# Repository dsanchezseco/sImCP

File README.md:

# **sImCP**

or *simple ICP* for the friends

sImCP is **custom PCB** powered by an atmega328p to emulate the different aircraft up front controlers (UFC) and input control panels (ICP), mainly a mix of the F-18 and the F-16 panels but with support for others like the AV-8B or the A-10C, for flight simming in DCS an other simulators.

The origin of the project was to have something in the empty space of the MFD in my cockpit, and as such the holes align with the holes and mounting of the Thrustmaster MFDs

The features that define the **sImCP** are:

* Atmega328p
* USB-C
* 21 keys (MX or ALPS mechanical switches)
* 2 encoders with push
* 1 2-Way switch
* 1 4-Way with push and encoder (called dobber)
* [QMK](https://qmk.fm) support
* Thrustmaster Cougar MFD mountable

In fact it is a **fully programmable keyboard** and as such its keys behaviour can be changed by creating a new custom keymap with QMK and flashing it to the board

### It is a keyboard, so use the keyboard column on DCS to do the keybinds

### **Default keymap**

The default keymap has the following keycodes:

```

   ------------ ----------- ------------- ------------- ------------
   |  LCTL+A  | |  LCTL+O  | |  LCTL+U  | |  LCTL+I   | |  LCTL+D  |
   ------------ ------------ ------------ ------------- ------------
   ------------ ------------ ------------ ------------- ------------
   |  RCTL+1  | |  RCTL+2  | |  RCTL+3  | | ENCODER 1 | |  LCTL+H  |
   ------------ ------------ ------------ ------------- ------------
   ------------ ------------ ------------ ------------- ------------
   |  RCTL+4  | |  RCTL+5  | |  RCTL+6  | | ENCODER 2 | |  LCTL+T  | 
   ------------ ------------ ------------ ------------- ------------
   ------------ ------------ ------------ ------------- ------------
   |  RCTL+7  | |  RCTL+8  | |  RCTL+9  | |  2-WAY    | |  LCTL+N  |
   ------------ ------------ ------------ ------------- ------------
   ------------ ------------ ------------ ------------- ------------
   |  RCTL+]  | |  LCTL+0  | |  RCTL+[  | |  DOBBER   | |  LCTL+;  |
   ------------ ------------ ------------ ------------- ------------

#########################################
   ENCODER 1
#########################################
  RCTL+F   LCTL+Q    RCTL+C
   (         |         )
   v         v         v

#########################################
   ENCODER 2
#########################################
  RCTL+Y   LCTL+J    RCTL+G
   (         |         )
   v         v         v

#########################################
   2-WAY
#########################################
  LCTL+K
    ^
    |

    |
    v
  LCTL+X

#########################################
   DOBBER
#########################################
          LCTL+M                     
            ^                        
            |                       RCTL+B   RCTL+W    RCTL+Z 
LCTL+P <-       -> LCTL+R            (         |         )
            |                        v         v         v
            v
          LCTL+W
```

### **Gamepad**

Instead of being recognised as a keyboard the sImCP can be flashed with a custom made firmware to act as a gamepad and output a button instead a keycode on each of the keys. 

**This feature is currently WIP**

### **Flashing** 

To flash a new keymap refeer to the [FIRMWARE README.md](READY%20TO%20USE%20FILES/FIRMWARE/README.md) under the `READY TO USE FILES` folder. The default keymap file is provided as well in the same folder.

### READY TO USE inventory

* PCB_FABRICATION: what's needed to order more to JLCPCB already in the correct format
* PCB_3DMODEL: in case you want to print something :)
* FIRMWARE: the code to make it running ready to flash
* 3D_PRINTABLES: stuff ready to print like the **dobber cap (by Joghurt - thanks!)**

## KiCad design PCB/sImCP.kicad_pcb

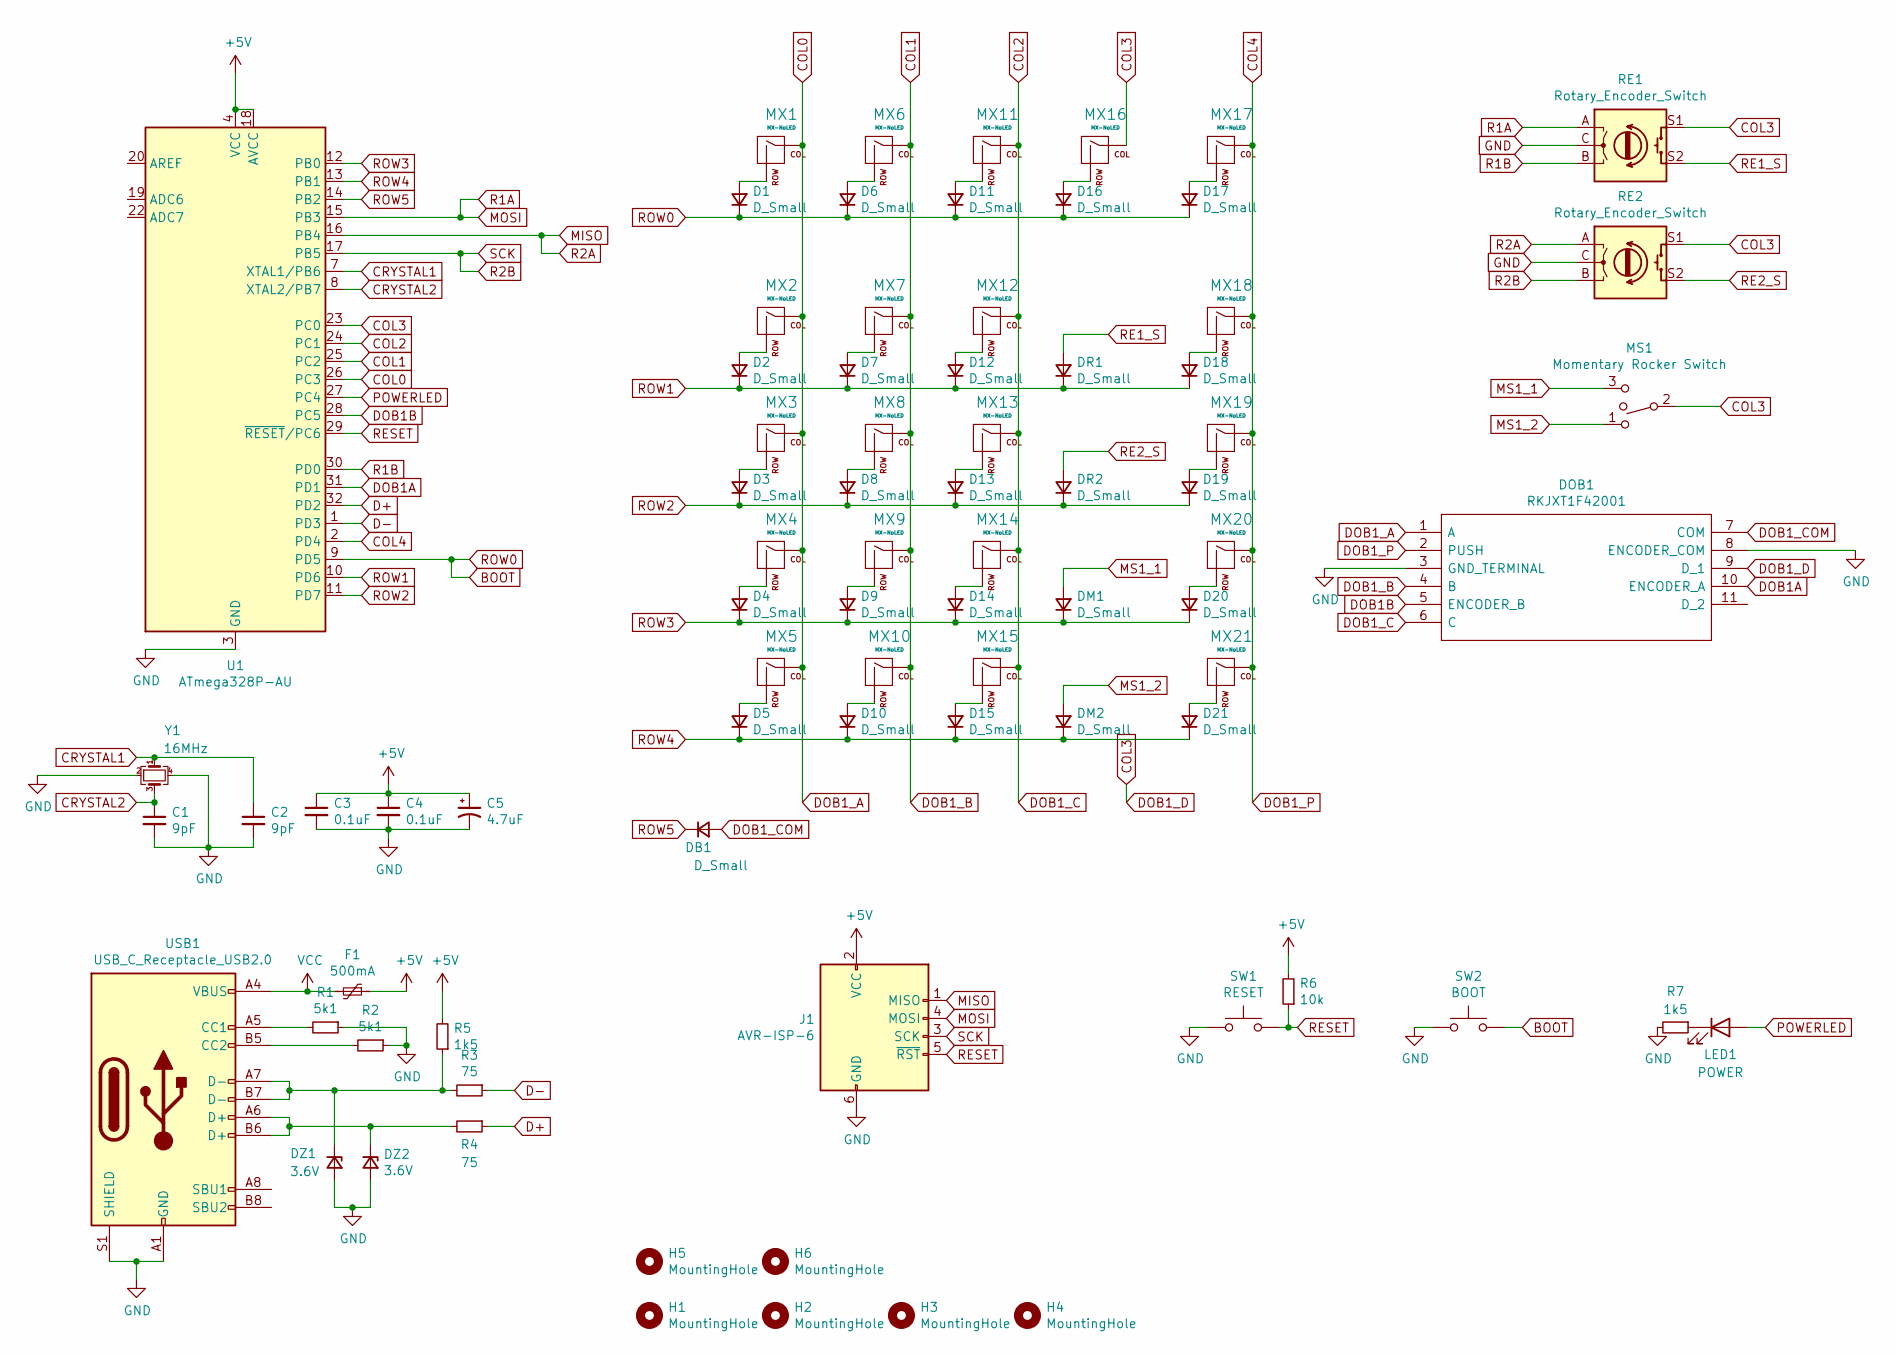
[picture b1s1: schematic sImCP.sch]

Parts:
C1, C2: 9pF; C_0402_1005Metric; LCSC C111805
C3, C4: 0.1uF; C_0603_1608Metric; LCSC C14663
C5: 4.7uF; CP_Radial_D4.0mm_P1.50mm; LCSC C47879
D1, D2, D3, D4, D5, D6, D7, D8, D9, D10, D11, D12, D13, D14, D15, D16, D17, D18, D19, D20, D21: D_Small; D_SOD-123FL; LCSC C426570
DB1: D_Small; D_SOD-123FL; LCSC C426570
DM1, DM2: D_Small; D_SOD-123FL; LCSC C426570
DOB1: RKJXT1F42001; Mouser Part Number 688-RKJXT1F42001
DR1, DR2: D_Small; D_SOD-123FL; LCSC C426570
DZ1, DZ2: 3.6V; D_SOD-123; LCSC C82565
F1: 500mA; C_Disc_D5.0mm_W2.5mm_P5.00mm; LCSC C208476
H1, H2, H3, H4: MountingHole; MountingHole_3.2mm_M3_ISO7380_Pad
H5, H6: MountingHole; MountingHole_2.2mm_M2_DIN965_Pad
J1: AVR-ISP-6; Reset_Pretty-Mask
LED1: POWER; LED_0805_2012Metric; LCSC C205442
MS1: Momentary Rocker Switch; RockerSwitch
MX1, MX2, MX3, MX4, MX5, MX6, MX7, MX8, MX9, MX10, MX11, MX12, MX13, MX14, MX15, MX16, MX17, MX18, MX19, MX20, MX21: MX-NoLED; MX-1U-NoLED; LCSC C400228
R1, R2: 5k1; R_0603_1608Metric; LCSC C23186
R3, R4: 75; R_0603_1608Metric; LCSC C4275
R5, R7: 1k5; R_0603_1608Metric; LCSC C22843
R6: 10k; R_0603_1608Metric; LCSC C25804
RE1, RE2: Rotary_Encoder_Switch; RotaryEncoder_Alps_EC11E-Switch_Vertical_H20mm; LCSC C255515
SW1: RESET; PinHeader_1x02_P1.27mm_Vertical
SW2: BOOT; PinHeader_1x02_P1.27mm_Vertical
U1: ATmega328P-AU; TQFP-32_7x7mm_P0.8mm; LCSC C14877
USB1: USB_C_Receptacle_USB2.0; USB_C_Receptacle_XKB_U262-16XN-4BVC11; LCSC C393939
Y1: 16MHz; Crystal_SMD_2520-4Pin_2.5x2.0mm; LCSC C280090

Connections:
+5V: C3.1, C4.1, C5.1, F1.1, J1.2 (VCC), R5.2, R6.2, U1.4 (VCC), U1.6 (VCC), U1.18 (AVCC)
BOOT: D1.1 (K), D6.1 (K), D11.1 (K), D16.1 (K), D17.1 (K), SW2.2, U1.9 (PD5)
COL0: DOB1.1 (A), MX1.1 (COL), MX2.1 (COL), MX3.1 (COL), MX4.1 (COL), MX5.1 (COL), U1.26 (PC3)
COL1: DOB1.4 (B), MX6.1 (COL), MX7.1 (COL), MX8.1 (COL), MX9.1 (COL), MX10.1 (COL), U1.25 (PC2)
COL2: DOB1.6 (C), MX11.1 (COL), MX12.1 (COL), MX13.1 (COL), MX14.1 (COL), MX15.1 (COL), U1.24 (PC1)
COL3: DOB1.9 (D_1), MS1.2, MX16.1 (COL), RE1.S1, RE2.S1, U1.23 (PC0)
COL4: DOB1.2 (PUSH), MX17.1 (COL), MX18.1 (COL), MX19.1 (COL), MX20.1 (COL), MX21.1 (COL), U1.2 (PD4)
CRYSTAL1: C2.1, U1.7 (XTAL1/PB6), Y1.1
CRYSTAL2: C1.1, U1.8 (XTAL2/PB7), Y1.3
D+: R4.1, U1.32 (PD2)
D-: R3.1, U1.1 (PD3)
DOB1A: DOB1.10 (ENCODER_A), U1.31 (PD1)
DOB1B: DOB1.5 (ENCODER_B), U1.28 (PC5)
DOB1_COM: DB1.2 (A), DOB1.7 (COM)
GND: C1.2, C2.2, C3.2, C4.2, C5.2, DOB1.3 (GND_TERMINAL), DOB1.8 (ENCODER_COM), DZ1.2 (A), DZ2.2 (A), J1.6 (GND), R1.1, R2.1, R7.2, RE1.C, RE2.C, SW1.1, SW2.1, U1.3 (GND), U1.5 (GND), U1.21 (GND), USB1.A1 (GND), USB1.A12 (GND), USB1.B1 (GND), USB1.B12 (GND), USB1.S1 (SHIELD), Y1.2, Y1.4
MISO: J1.1 (MISO), RE2.A, U1.16 (PB4)
MOSI: J1.4 (MOSI), RE1.A, U1.15 (PB3)
MS1_1: DM1.2 (A), MS1.3
MS1_2: DM2.2 (A), MS1.1
unnamed: D1.2 (A), MX1.2 (ROW)
unnamed: D2.2 (A), MX2.2 (ROW)
unnamed: D3.2 (A), MX3.2 (ROW)
unnamed: D4.2 (A), MX4.2 (ROW)
unnamed: D5.2 (A), MX5.2 (ROW)
unnamed: D6.2 (A), MX6.2 (ROW)
unnamed: D7.2 (A), MX7.2 (ROW)
unnamed: D8.2 (A), MX8.2 (ROW)
unnamed: D9.2 (A), MX9.2 (ROW)
unnamed: D10.2 (A), MX10.2 (ROW)
unnamed: D11.2 (A), MX11.2 (ROW)
unnamed: D12.2 (A), MX12.2 (ROW)
unnamed: D13.2 (A), MX13.2 (ROW)
unnamed: D14.2 (A), MX14.2 (ROW)
unnamed: D15.2 (A), MX15.2 (ROW)
unnamed: D16.2 (A), MX16.2 (ROW)
unnamed: D17.2 (A), MX17.2 (ROW)
unnamed: D18.2 (A), MX18.2 (ROW)
unnamed: D19.2 (A), MX19.2 (ROW)
unnamed: D20.2 (A), MX20.2 (ROW)
unnamed: D21.2 (A), MX21.2 (ROW)
unnamed: DZ1.1 (K), R3.2, R5.1, USB1.A7 (D-), USB1.B7 (D-)
unnamed: DZ2.1 (K), R4.2, USB1.A6 (D+), USB1.B6 (D+)
unnamed: LED1.1 (K), R7.1
unnamed: R1.2, USB1.A5 (CC1)
unnamed: R2.2, USB1.B5 (CC2)
POWERLED: LED1.2 (A), U1.27 (PC4)
R1B: RE1.B, U1.30 (PD0)
R2B: J1.3 (SCK), RE2.B, U1.17 (PB5)
RE1_S: DR1.2 (A), RE1.S2
RE2_S: DR2.2 (A), RE2.S2
RESET: J1.5 (~RST), R6.1, SW1.2, U1.29 (~RESET~/PC6)
ROW1: D2.1 (K), D7.1 (K), D12.1 (K), D18.1 (K), DR1.1 (K), U1.10 (PD6)
ROW2: D3.1 (K), D8.1 (K), D13.1 (K), D19.1 (K), DR2.1 (K), U1.11 (PD7)
ROW3: D4.1 (K), D9.1 (K), D14.1 (K), D20.1 (K), DM1.1 (K), U1.12 (PB0)
ROW4: D5.1 (K), D10.1 (K), D15.1 (K), D21.1 (K), DM2.1 (K), U1.13 (PB1)
ROW5: DB1.1 (K), U1.14 (PB2)
VCC: F1.2, USB1.A4 (VBUS), USB1.A9 (VBUS), USB1.B4 (VBUS), USB1.B9 (VBUS)

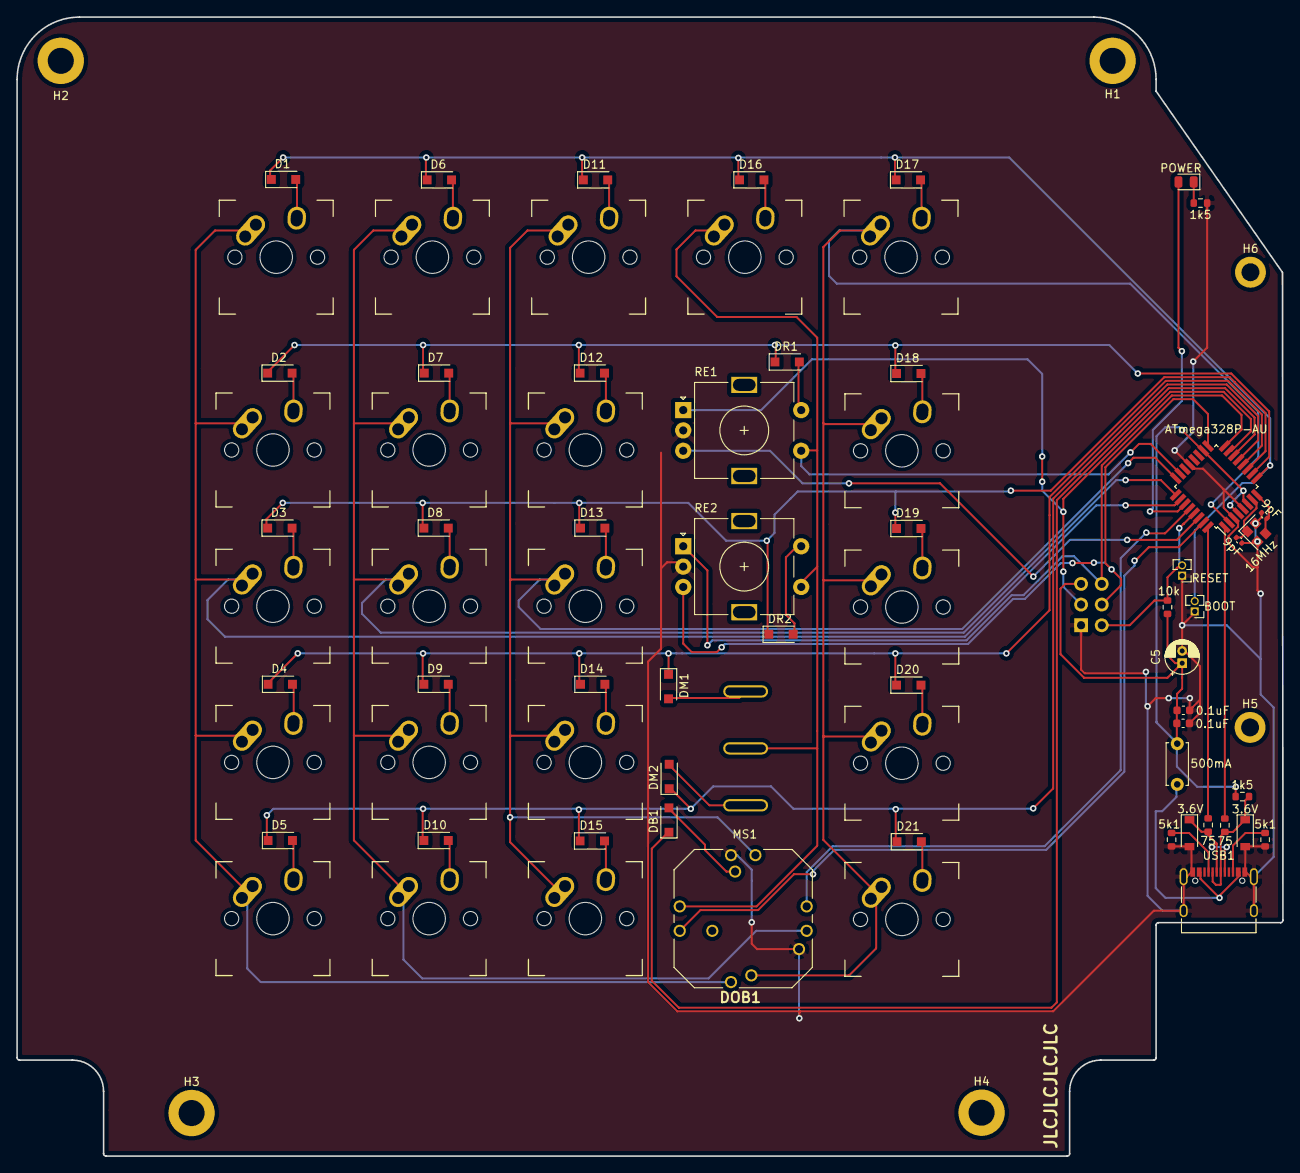
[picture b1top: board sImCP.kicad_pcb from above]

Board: 2 copper layers, 155.6 x 140.0 mm, 79 parts (1 on the bottom side), 57 nets.

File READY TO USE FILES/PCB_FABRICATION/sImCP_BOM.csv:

Comment,Designator,Footprint,LCSC
"9pF","C1,C2","Capacitor_SMD:C_0402_1005Metric","C111805"
"0.1uF","C3,C4","Capacitor_SMD:C_0603_1608Metric","C14663"
"4.7uF","C5","Capacitor_SMD:CP_Elec_4x5.3","C107392"
"D_Small","D1,DR1,DM1,DB1,D2,DR2,DM2,D3,D4,D5,D6,D7,D8,D9,D10,D11,D12,D13,D14,D15,D16,D17,D18,D19,D20,D21","Diode_SMD:D_SOD-123F","C426570"
"RKJXT1F42001","DOB1","ALPS_RKJXT1F42001:RKJXT1F42001","C160841"
"3.6V","DZ1,DZ2","Diode_SMD:D_SOD-123","C82565"
"500mA","F1","Capacitor_SMD:C_1206_3216Metric_Pad1.33x1.80mm_HandSolder","C845298"
"MountingHole","H1,H2,H3,H4","MountingHole:MountingHole_3.2mm_M3_ISO7380_Pad",""
"AVR-ISP-6","J1","random-keyboard-parts:Reset_Pretty-Mask",""
"POWER","LED1","LED_SMD:LED_0805_2012Metric"," 	C205442"
"Momentary Rocker Switch","MS1","",""
"MX-NoLED","MX1,MX2,MX3,MX4,MX5,MX6,MX7,MX8,MX9,MX10,MX11,MX12,MX13,MX14,MX15,MX16,MX17,MX18,MX19,MX20,MX21","MX_Alps_Hybrid:MX-1U-NoLED","C400228"
"5k1","R1,R2","Resistor_SMD:R_0603_1608Metric","C23186"
"75","R3,R4","Resistor_SMD:R_0603_1608Metric","C4275"
"1k5","R5,R7","Resistor_SMD:R_0603_1608Metric","C22843"
"10k","R6","Resistor_SMD:R_0603_1608Metric","C25804"
"Rotary_Encoder_Switch","RE1,RE2","Rotary_Encoder:RotaryEncoder_Alps_EC11E-Switch_Vertical_H20mm"," 	C255515"
"RESET","SW1","Connector_PinHeader_1.00mm:PinHeader_1x02_P1.00mm_Vertical",""
"BOOT","SW2","Connector_PinHeader_1.00mm:PinHeader_1x02_P1.00mm_Vertical",""
"ATmega328P-AU","U1","Package_QFP:TQFP-32_7x7mm_P0.8mm","C14877"
"USB_C_Receptacle_USB2.0","USB1","Connector_USB:USB_C_Receptacle_XKB_U262-16XN-4BVC11","C393939"
"16MHz","Y1","Crystal:Crystal_SMD_2520-4Pin_2.5x2.0mm"," 	C280090"

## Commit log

2021-05-13 Proyect start
2021-05-13 Started electrical diagram
    Added switches and random keyboard parts libs
    Added sketch of components placement
2021-05-13 added extra row for the 5-way
2021-05-14 added rest of the components
    using atmega328p with an USB-C and SMD components
    Dobber is missing
2021-05-15 Added dobber symbol and footprint and wiring
    added footprint for missing components, missing rocker switch
2021-05-15 added more footprint associations
2021-05-15 Start of pcb components placement
2021-05-15 not needed
2021-05-15 updated switches footprints lib, start of placement on board
2021-05-15 more component placement on the pcb
2021-05-16 trace routing
2021-05-16 more routing, only dobber and 2-way missing
2021-05-17 updated with all SMD on the front and part numbers for production
2021-05-17 updated silk values to be printed
2021-05-17 updated footprint for boot and reset headers
2021-05-18 added dobber's encoder connection to MCU
2021-05-18 routed dobber and renamed files to sImCP
2021-05-18 moved all to root
2021-05-18 added rocker switch footprint
2021-05-18 added new 3dmodels
2021-05-18 added some artwork
2021-05-18 special parts spaced out
2021-05-18 added rocker switch 3dmodel
2021-05-18 fixed libs path
2021-05-18 added keycaps to switches
2021-05-18 added encoder knob 3d model
2021-05-19 update diode footprint to SOD-123FL
2021-05-19 changed USB-C 3dmodel
2021-05-19 update rocker switch 3dmodel
2021-05-19 updated dobber 3dmodel
2021-05-19 added dobber cap made by Joghurt - thanks!!
2021-05-19 changed wiring to encoders sharing pins
2021-05-19 repo reorg
2021-05-19 submodules re-add
2021-05-19 added folder for ready to use files
2021-05-19 added BOM
2021-05-19 Dobber cap printable by Joghurt
2021-05-19 rerouted with new encoder wiring
2021-05-19 fabrication files for pcb
2021-05-31 fixed encoders mess, wiring missing
2021-06-07 updated pcb with new routing for the encoders
    now using a set of pins for each encoder instead of the shared model
2021-06-09 updated step file for 3d model of pcb
2021-06-29 Fixed path for random keyboard parts
2021-06-29 added backlight leds and control mosfet
2021-09-04 feat: changed MX footprint to two holes
    Changed MX footprints for easier soldering without platE
    added .DS_Store to .gitignore
2021-09-04 [FAB FILES] feat: changed 4u7 capacitor to THT
    Changed capacitor to THT as previous part number has no stock
    Regenerated fabrication files
2021-10-15 updated .gitignore
2021-10-15 feat: added firmware with bootloader and qmk firmware
2021-10-16 feat: qmk firmware updated
2021-10-16 feat: added image
2021-10-16 feat: updated readme with flashing intructions
2021-10-16 fix: showing images
2021-10-16 fix: image order
2021-10-16 feat: updated README
2021-10-16 fix: image url in readme
2021-10-16 feat: updated qmk firmware
2021-10-17 hex clean
2021-10-17 hex put back
2021-10-23 feat: added bootloader file with keymap
